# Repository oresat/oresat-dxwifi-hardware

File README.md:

# oresat-dxwifi-hardware
This repository is for the DxWiFi hardware that will fly on the OreSat satellite. DxWiFi is our communication subsystem for high speed data (1 Mbps) using 2.4 GHz WiFi between the spacecraft and ground.

This is hardware for the **satellite** only; please see the other repos if you're looking for the [OreSat Live Handheld Ground Station](https://github.com/oresat/oresat-live-handheld-ground-station) or the [Mini-OreSat testing platform for high altitude balloons](https://github.com/oresat/oresat-live-mini-oresat).

We intend to use "ordinary WiFi" (IEEE 802.11b) as a high speed satellite communication system. What is _not_ ordinary is that we run the radio under the amateur radio rules and regulations (FCC Part 97) and thus can increase power levels and antenna gains necessary to make the link budget work.

### Ordinary WiFi
The plan is to use the Qualcomm Atheros AR9271 USB to WiFi adapter because of the driver support in Linux.

### Non ordinary bi-directional power amplifier
This project is intended to operate under the Amateur Radio Service [47CFR97](https://www.gpo.gov/fdsys/pkg/CFR-1996-title47-vol5/pdf/CFR-1996-title47-vol5-part97.pdf) whereby larger power levels and higher gain directional antennas can be used within the [13 cm band](https://en.wikipedia.org/wiki/13-centimeter_band) to close the link.

NB:  There are other DxWiFi materials on the PSAS GitHub repo, but those repos are deprecated.

Link budgets can be found [here](https://github.com/oresat/oresat-dxwifi-hardware/tree/master/Link-Model).

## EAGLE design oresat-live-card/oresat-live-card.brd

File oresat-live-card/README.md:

---
title: "**OreSat Live / DxWiFi Card**"
subtitle: |
  **Fabrication and Assembly Information**\
  For build TIME-STAMP
fontsize: 10pt
geometry:
  - margin=0.5in
toc: true
toc-depth: 2
colorlinks: true
urlcolor: blue
---

\newpage

# About this Board

## Board Description

TODO: DESCRIBE CARD

## Documentation Links

- OL hardware Git repository: <https://github.com/oresat/oresat-dxwifi-hardware>
- OL software Git reposity: <https://github.com/oresat/oresat-dxwifi-software>
- **TODO:** OL Design Notes + Design Review Notes

## Documentation Files

| Filename                        | Notes                                    |
| ------------------------------- | ---------------------------------------- |
| README.pdf                      | This README file                         |
| PROJECT-NAME-outline.dxf        | Board outline (with holes) in DXF format |
| PROJECT-NAME-pcba.step          | 3D model of PCBA (with components)       |
| PROJECT-NAME-render-bot.jpg     | Render of the top of the 3D model        |
| PROJECT-NAME-render-bot.jpg     | Render of the bottom of the 3D model     |
| PROJECT-NAME-schematic.pdf      | PDF of board schematics                  |

## Contact Information

- Website: <https://www.oresat.org/>
- Email: <oresat@pdx.edu>
- Instagram: @pdxaerospace

## Board Renders

{width=50%}
{width=50%}

\newpage

# Printed Circuit Board (PCB) Fabrication Information

## Board Info

- 4 layer board
- Bounding box is 99.8 x 94.6 mm (3.93 x 3.72 in)
- Board thickness is 1.59 mm (0.063 inch)
- **Important:** See Materials and Stack Up sections below

## Board Requirements

- Design Rules
    - Minimum Trace / Space design rules
       - Outer layers: 0.127 mm (5.0 mil) / 0.127 mm (5.0 mil)
       - Inner layers: 0.127 mm (5.0 mil) / 0.127 mm (5.0 mil)
    - Outer dimension router tolerance: +/- 0.254 mm (10.0 mil)
    - Hole placement tolerance: +/- 0.075 mm (3.0 mil)
    - Inner tab routed slot tolerance: +/- 0.254 mm (10.0 mil)
- Drills
   - Drill Positional Tolerance: 0.051 mm (2.0 mil)
   - Drill Size tolerance: +/- 0.064 mm (2.5 mil)
- Plated/Un-plated holes
  - There are 6 un-plated (NPT) holes
  - There are 1477 plated through (PTH) holes
  - PTH minimum diameter: 0.254 mm (10 mil)
  - PTH minimum annulus: 0.102 mm (4 mil) radius
- Outline/Routing
  - Requires a 1.0 mm or smaller diameter routing bit
- Slots
  - There are no slots.
- Cutouts
  - There are no cutouts
- There are 3 fiducials on the top layer and 3 on the bottom layer.
- Panel tabs ("mouse bites")
   - Card edges must be smooth; no mouse bites or other intrusions into the card outline.
   - If external mouse bites are required, minimize and customer will remove by hand before assembly.
- If not otherwise specified, build to IPC 6012 Class 2 or better.

## Materials

- Controlled impedance
   - The stackup is critical for the performance of high speed signals on this board.
   - As long as the stackup is controlled, the board is not considered controlled impedance.
- Isola FR408HR or material with equivalent Dk.
- Board Surface treatment should be ENIG, althogh immersion Silver is acceptable.
- White silkscreen on top and bottom surface
- Taiyo PSR-4000 or equivalent soldermask on top and bottom, no requirements for color.

## Stack Up

| Layer         | Thickness           | Notes                                        |
|---------------|---------------------|----------------------------------------------|
| Top Copper    | 0.043 mm /  1.7 mil |  Layer 1 foil, 1 oz Cu after plating         |
| prepreg       | 0.200 mm /  7.9 mil |  Prepreg - Isola FR408HR 2113                |
| Layer 2       | 0.018 mm /  0.7 mil |  Layer 2 foil, 0.5 oz Cu                     |
| Core          | 0.991 mm /   39 mil |  Core Isola FR408HR                          |
| Layer 3       | 0.018 mm /  0.7 mil |  Layer 3 foil, 0.5 oz Cu                     |
| prepreg       | 0.200 mm /  7.9 mil |  Prepreg - Isola FR408HR 2113                |
| Bottom Copper | 0.043 mm /  1.7 mil |  Layer 4 foil, 1 oz copper after plating     |
| **Total Stackup** | **1.588 mm / 62.5 mil** |                                      |

## Array / Panel Information

- Coordinate with Contract Manufacturer (CM) for optimal size of this panel.
- If no feedback from CM, then produce single boards (no panel).

## Fabrication Files

### IPC-2581 File

| Filename                 | Notes                                   |
| ------------------------ | --------------------------------------- |
| PROJECT-NAME-ipc2581.xml | IPC-2581 board information file         |

### Legacy PCB Files

| Filename                      | Notes                                         |
| ------------------------------| --------------------------------------------- |
| PROJECT-NAME-Edge_Cuts.gbr    | RS274X file for the dimension (outline) layer |
| PROJECT-NAME-F_Silkscreen.gbr | RS274X file for the top silkscreen            |
| PROJECT-NAME-F_Mask.gbr       | RS274X file for the top soldermask            |
| PROJECT-NAME-F_Cu.gbr         | RS274X file for the top copper layer          |
| PROJECT-NAME-In1_Cu.gbr       | RS274X file for the layer 2 copper            |
| PROJECT-NAME-In2_Cu.gbr       | RS274X file for the layer 3 copper            |
| PROJECT-NAME-B_Cu.gbr         | RS274X file for the bottom copper layer       |
| PROJECT-NAME-B_Mask.gbr       | RS274X file for the bottom soldermask         |
| PROJECT-NAME-B_Silkscreen.gbr | RS274X file for the bottom silkscreen         |
| PROJECT-NAME-NPTH.drl         | Excellon file for non-plated through holes    |
| PROJECT-NAME-PTH.drl          | Excellon file for plated through holes        | 

\newpage

# Printed Circuit Board Assembly (PCBA) Information

## Assembly Info

- There are components are on the top and bottom side of the board.
- This PCBA is mostly surface mount (SMT) with a few (THT) components.

## Assembly Requirements

- Assemble to IPC Class 2 or better
- Bake components that are not moisture sealed to appropriate levels as required.
- Solder paste MUST be leaded.
- Aqueous flux and wash strongly preferred.
   - Clean to NASA Standard "Visibly Clean (VC)": No particles or residues are visible to the naked eye.
- No conformal coating.
- Ship in antistatic protective bag

## Component Specific Assembly Information

- SMPM connectors (J3, J4) should be hand-added according to the Oresat SOP.

## Assembly Files

### IPC-2581 File

| Filename                 | Notes                           |
| ------------------------ | ------------------------------- |
| PROJECT-NAME-ipc2581.xml | IPC-2581 board information file |

### Bill of Materials (BOM)

| Filename             | Description                            |
| -------------------- | -------------------------------------- |
| PROJECT-NAME-bom.csv | BOM in Comma Separated Variable format |

### Solder Paste Stencils

| Filename                 | Notes                                            |
| ------------------------ | ------------------------------------------------ |
| PROJECT-NAME-B_Paste.gbr | RS274X file for top/front solder paste stencil   |
| PROJECT-NAME-F_Paste.gbr | RS274X file for bottom/back solder paste stencil |

### Mounting/Placement Location

| Filename            | Description                                 |
| ------------------- | ------------------------------------------- |
| PROJECT-NAME-3u.pos | Pick and place locations for components     |

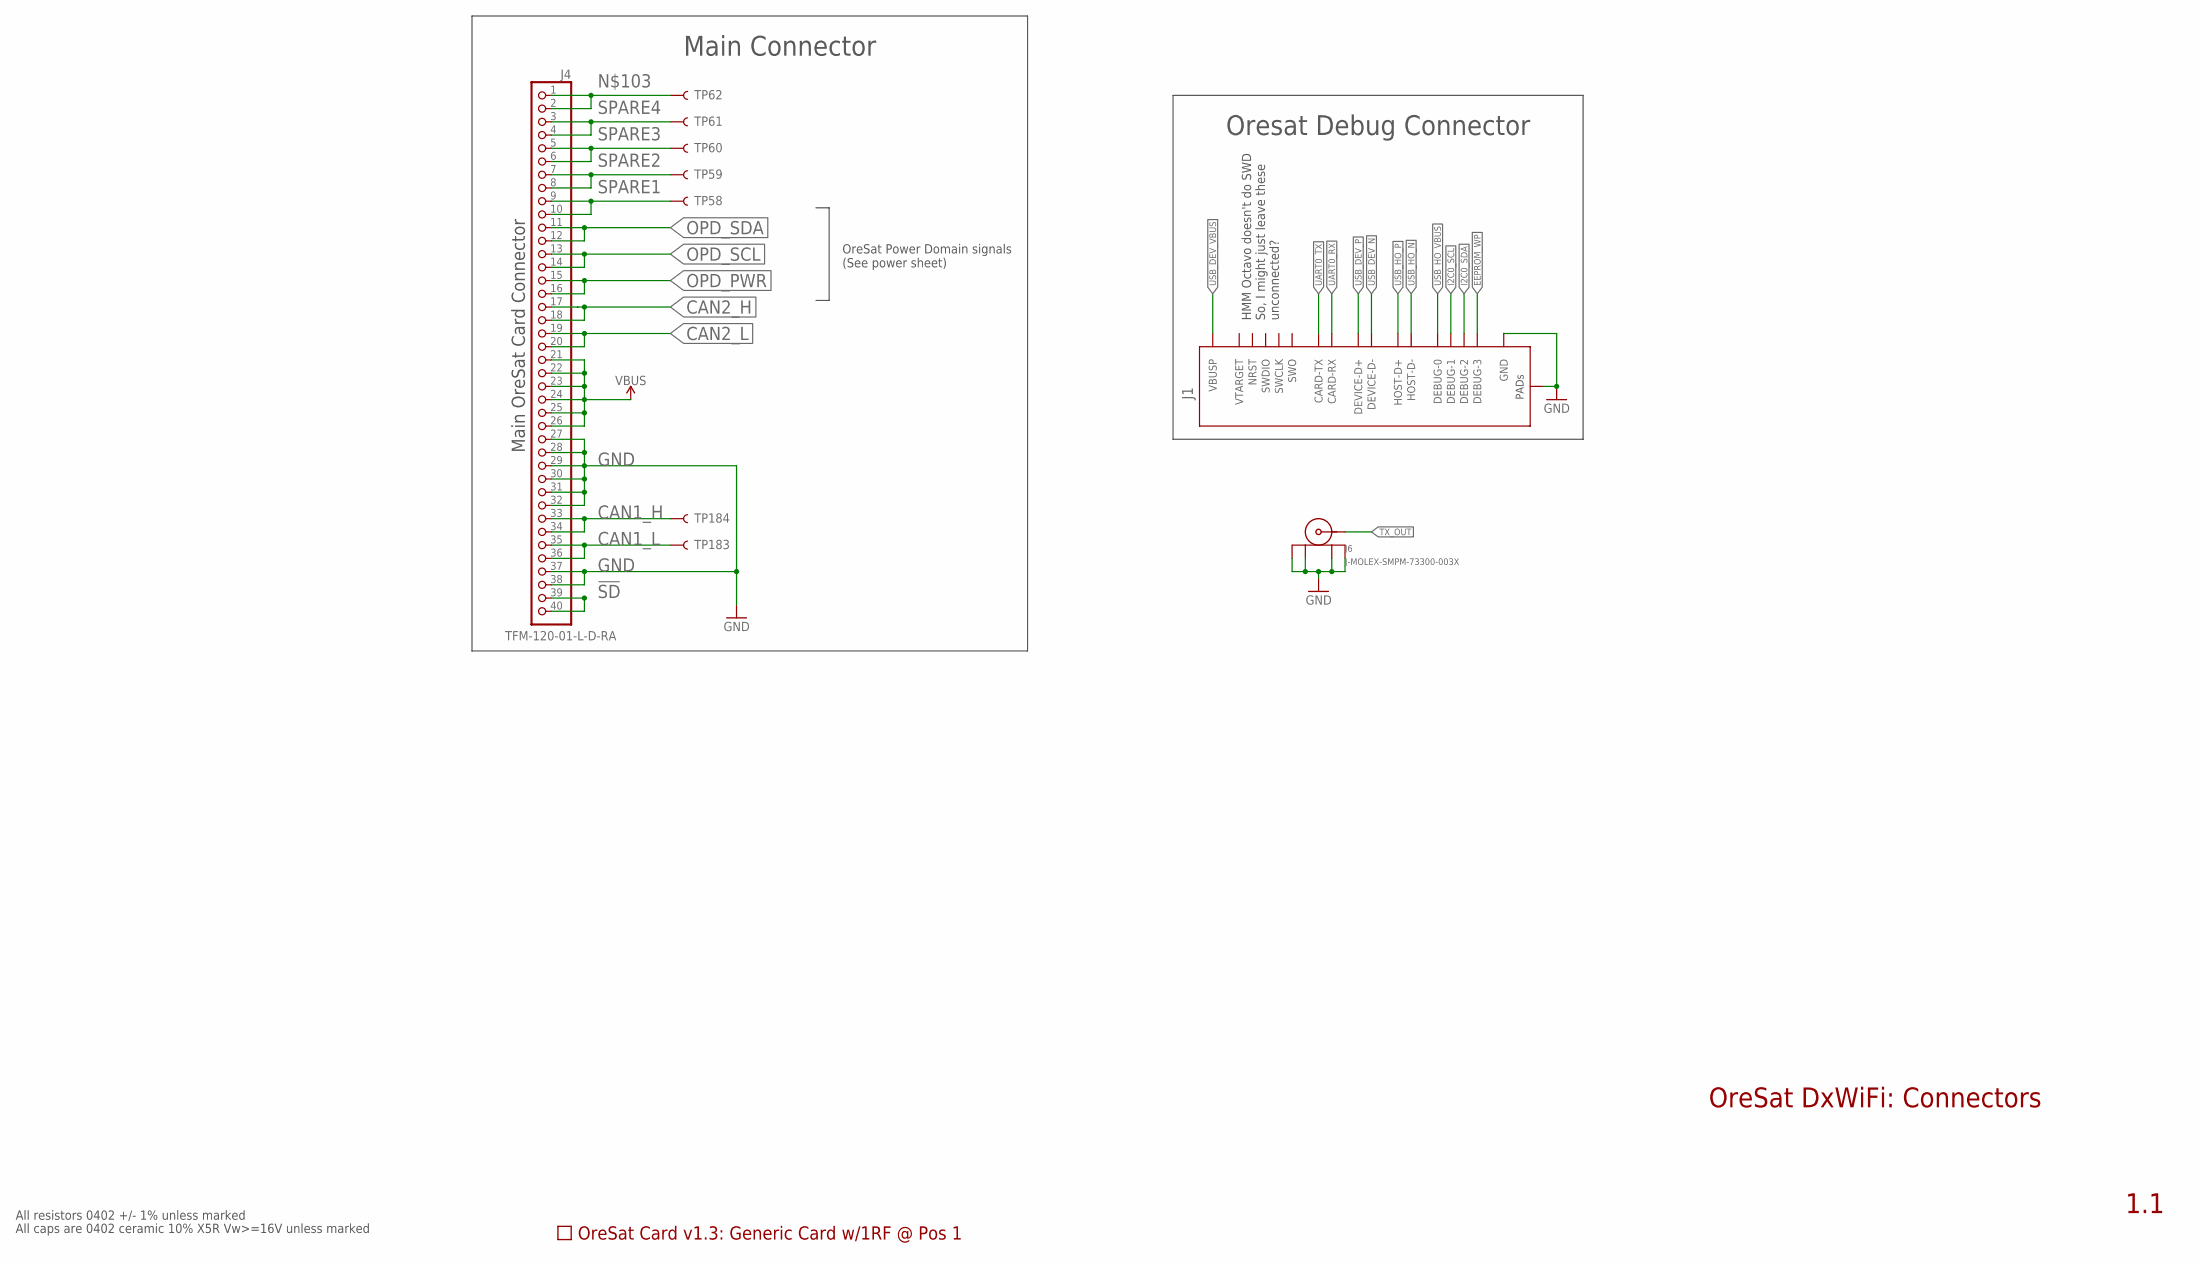
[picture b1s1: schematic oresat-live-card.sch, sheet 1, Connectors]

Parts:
J1: ORESAT-DEBUG-CONNECTOR-CARD; TE_2-1734592-0
J4: TFM-120-01-L-D-RA; J-SAMTEC-TFM-120-X1-XXX-D-RA
J6: J-MOLEX-SMPM-73300-003X; J-MOLEX-SMPM-073300-003X
PCB1: ORESAT-CARD-V1.3-GENERIC-1RF-POS1
TP58, TP59, TP60, TP61, TP62, TP183, TP184: TEST-POINT3X4; PAD.03X.04

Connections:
!SD: J4.39, J4.40
CAN1_H: J4.33, J4.34, TP184.1
CAN1_L: J4.35, J4.36, TP183.1
CAN2_H: J4.17, J4.18; also elsewhere on the board
CAN2_L: J4.19, J4.20; also elsewhere on the board
EEPROM_WP: J1.20 (DEBUG-3); also elsewhere on the board
GND: J1.3 (GND), J1.6 (GND), J1.9 (GND), J1.PAD1 (PAD), J1.PAD2 (PAD), J4.27, J4.28, J4.29, J4.30, J4.31, J4.32, J4.37, J4.38, J6.P$1 (SHIELD3), J6.P$2 (SHIELD2), J6.P$3 (SHIELD1), J6.P$4 (SHIELD); also elsewhere on the board
I2C0_SCL: J1.18 (DEBUG-1); also elsewhere on the board
I2C0_SDA: J1.19 (DEBUG-2); also elsewhere on the board
unnamed: J4.1, J4.2, TP62.1
OPD_PWR: J4.15, J4.16; also elsewhere on the board
OPD_SCL: J4.13, J4.14; also elsewhere on the board
OPD_SDA: J4.11, J4.12; also elsewhere on the board
SPARE1: J4.9, J4.10, TP58.1
SPARE2: J4.7, J4.8, TP59.1
SPARE3: J4.5, J4.6, TP60.1
SPARE4: J4.3, J4.4, TP61.1
TX_OUT: J6.RF (CENTER); also elsewhere on the board
UART0_RX: J1.12 (CARD-RX); also elsewhere on the board
UART0_TX: J1.13 (CARD-TX); also elsewhere on the board
USB_DEV_N: J1.5 (DEVICE-D-); also elsewhere on the board
USB_DEV_P: J1.4 (DEVICE-D+); also elsewhere on the board
USB_DEV_VBUS: J1.1 (VBUSP), J1.2 (VBUSP); also elsewhere on the board
USB_HO_N: J1.8 (HOST-D-); also elsewhere on the board
USB_HO_P: J1.7 (HOST-D+); also elsewhere on the board
USB_HO_VBUS: J1.17 (DEBUG-0); also elsewhere on the board
VBUS: J4.21, J4.22, J4.23, J4.24, J4.25, J4.26; also elsewhere on the board

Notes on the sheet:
OreSat DxWiFi: Connectors
1.1
All resistors 0402 +/- 1% unless marked
All caps are 0402 ceramic 10% X5R Vw>=16V unless marked
Main Connector
Main OreSat Card Connector
OreSat Power Domain signals (See power sheet)
HMM Octavo doesn't do SWD So, I might just leave these unconnected?
Oresat Debug Connector

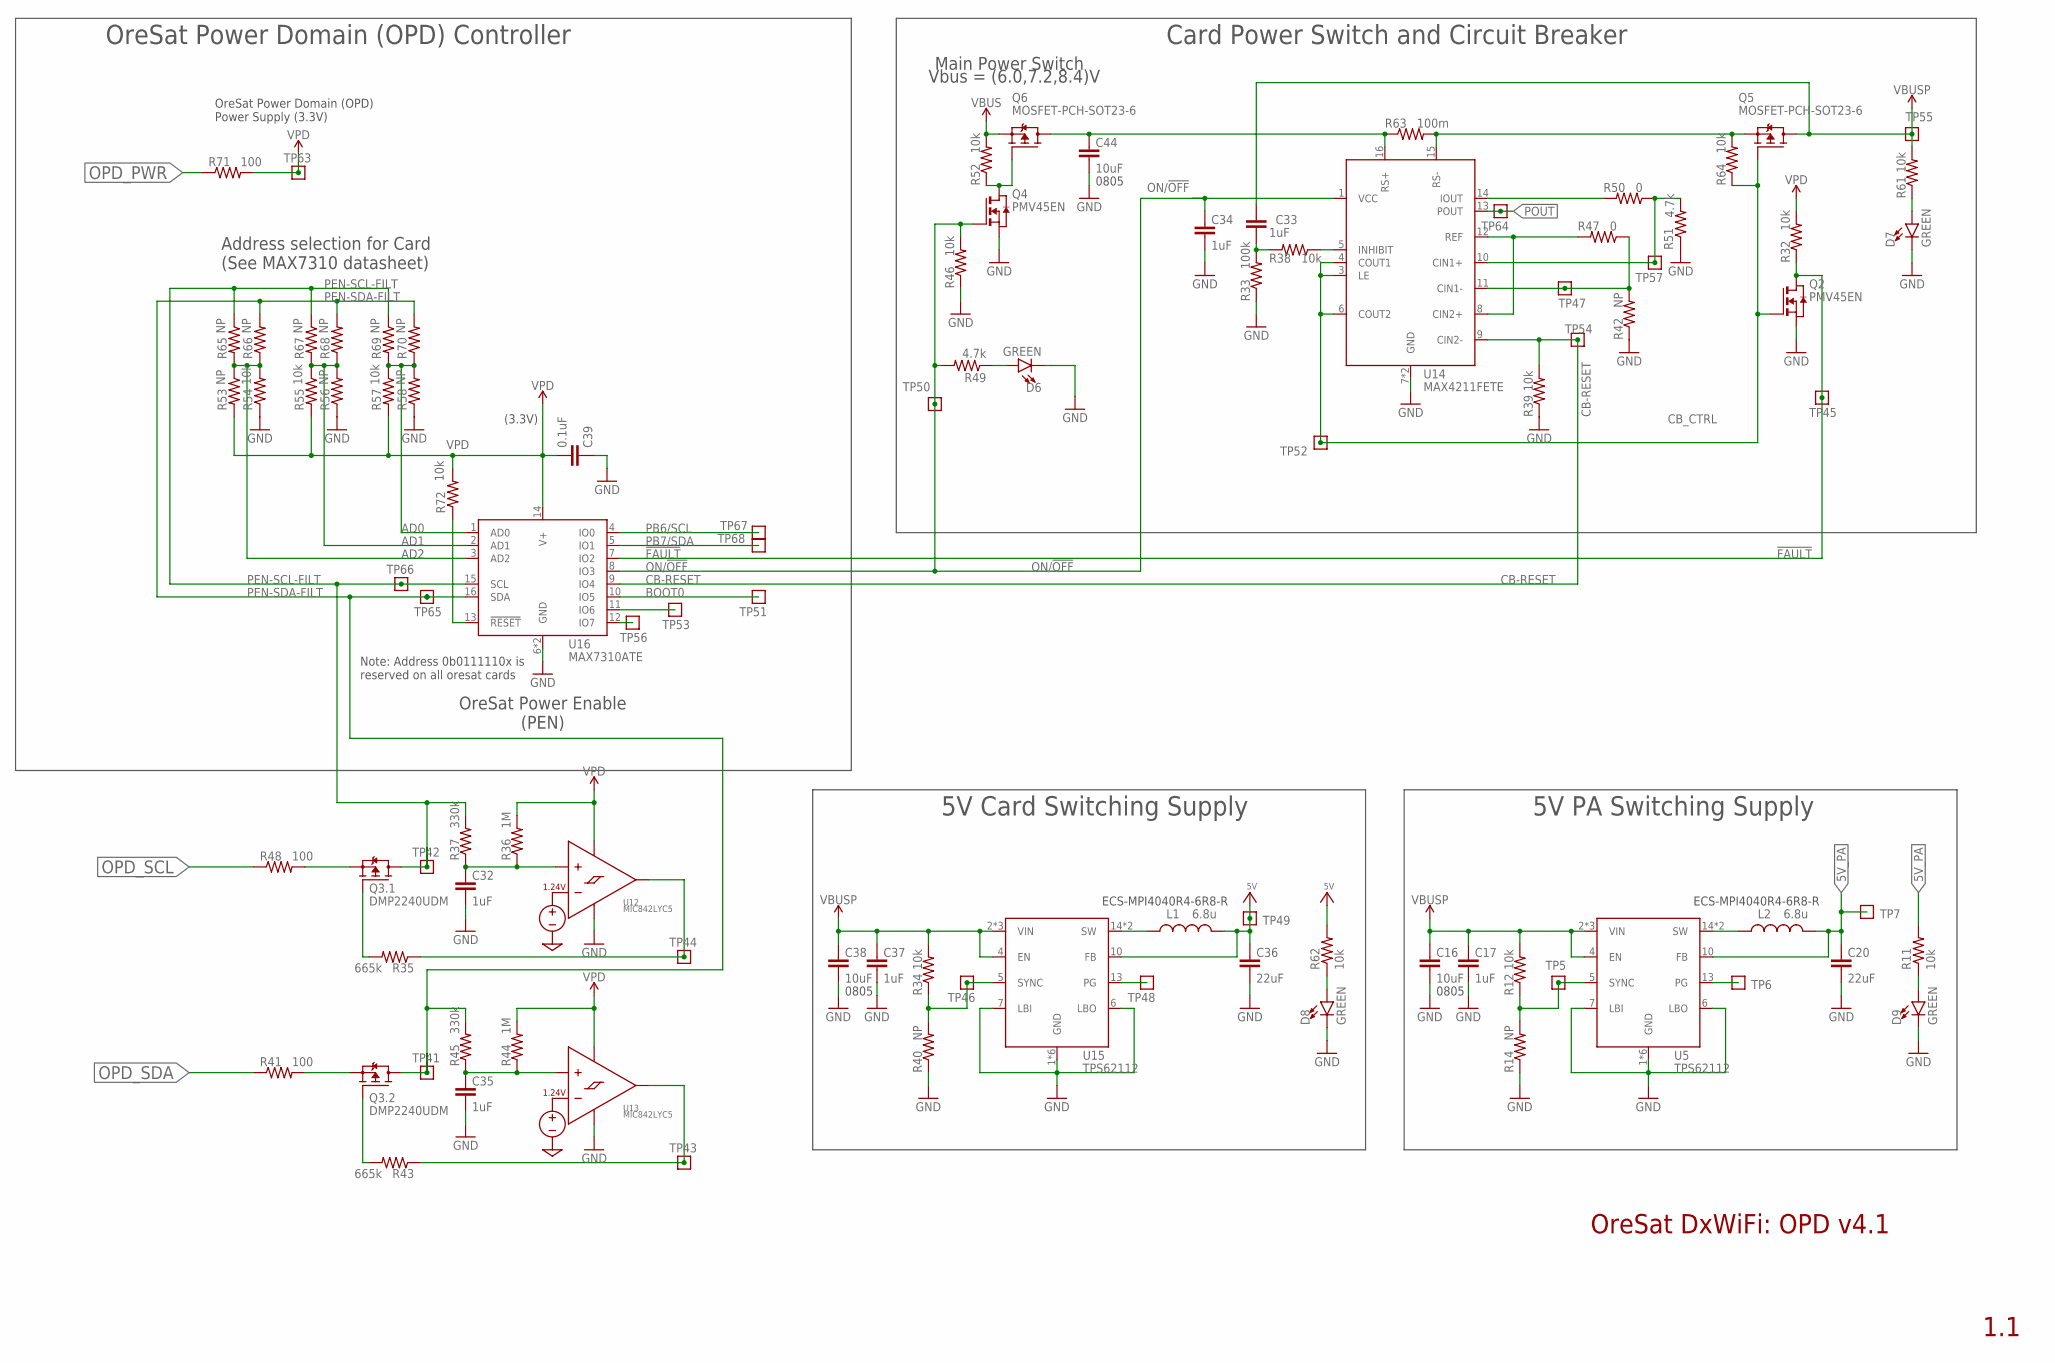
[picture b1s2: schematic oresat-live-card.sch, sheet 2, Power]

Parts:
C16, C38, C44: 10uF; .0805-B
C17, C34, C37: 1uF; .0603-A
C20: 22uF; C1210; MPN GCJ32ER71C226KE01L
C32, C35: 1uF; .0805-B-NOSILK
C33: 1uF; .0603-A; MPN CL05B104KO5NNNC
C36: 22uF; C1210
C39: 0.1uF; .0603-A
D6, D7, D9: GREEN; LED-0603; MANUFACTURER_PART_NUMBER 150060VS55040; DIGI-KEY_PART_NUMBER 732-12017-1-ND
D8: GREEN; LED-0603; MANUFACTURE_PART_NUMBER 150060VS55040; DIGI-KEY_PART_NUMBER 732-12017-1-ND
L1, L2: 6.8u; ECS-MPI4040
Q2, Q4: PMV45EN; SOT23; MPN PMV45EN2R
Q3: DMP2240UDM; SOT23-6
Q5, Q6: MOSFET-PCH-SOT23-6; SOT23-6; MPN DMP3050LVT-7
R11, R12, R32, R34, R39, R46, R52, R61, R62, R64, R72: 10k; .0603-A
R14, R40, R42, R53, R56, R58, R65, R66, R67, R68, R69, R70: NP; .0603-A; MPN RC1005F6653CS
R33: 100k; .0603-A; MPN RC1005F6653CS
R35, R43: 665k; .0603-A
R36, R44: 1M; .0603-A
R37, R45: 330k; .0603-A
R38, R54, R55, R57: 10k; .0603-A; MPN RC1005F6653CS
R41, R48, R71: 100; .0603-A
R47, R50: 0; .0603-A
R49: 4.7k; .0603-A
R51: 4.7k; .0603-A; MPN RC1005F6653CS
R63: 100m; R1206
TP5, TP6, TP7, TP41, TP42, TP43, TP44, TP45, TP46, TP47, TP48, TP49, TP50, TP51, TP52, TP53, TP54, TP55, TP56, TP57, TP63, TP64, TP65, TP66, TP67, TP68: TEST-POINT; 2MM-TEST-POINT
U5, U15: TPS62112; S-PVQFN-16
U12, U13: MIC842LYC5; SC70-5
U14: MAX4211FETE; QFN65P400X400X80-17T210
U16: MAX7310ATE; QFN65P400X400X80-17T210; MPN MAX7310ATE

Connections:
5V: C36.1, L1.2, R62.2, TP49.1, U15.10 (FB); also elsewhere on the board
5V_PA: C20.1, L2.2, R11.2, TP7.1, U5.10 (FB); also elsewhere on the board
!FAULT: Q2.3 (D), R32.1, TP45.1, U16.7 (IO2)
AD0: R57.1, R58.2, R69.2, R70.1, U16.1 (AD0)
AD1: R55.1, R56.2, R67.2, R68.1, U16.2 (AD1)
AD2: R53.1, R54.2, R65.2, R66.1, U16.3 (AD2)
BOOT0: TP51.1, U16.10 (IO5)
CB-RESET: R39.2, TP54.1, U14.9 (CIN2-), U16.9 (IO4)
CB_CTRL: Q2.1 (G), Q5.3 (G), R64.1, TP52.1, U14.3 (LE), U14.4 (COUT1), U14.6 (COUT2)
GND: C16.2, C17.2, C20.2, C32.2, C34.2, C35.2, C36.2, C37.2, C38.2, C39.1, C44.2, D6.C, D7.C, D8.C, D9.C, Q2.2 (S), Q4.2 (S), R14.1, R33.1, R39.1, R40.1, R42.1, R46.1, R51.1, R54.1, R56.1, R58.1, U5.1 (GND), U5.6 (LBO), U5.7 (LBI), U5.9 (GND), U5.11 (GND), U5.12 (GND), U5.16 (GND), U5.PAD (GND), U12.2 (GND), U13.2 (GND), U14.7 (GND), U14.EPAD (GND), U15.1 (GND), U15.6 (LBO), U15.7 (LBI), U15.9 (GND), U15.11 (GND), U15.12 (GND), U15.16 (GND), U15.PAD (GND), U16.6 (GND), U16.EPAD (GND); also elsewhere on the board
IOUT: R50.2, U14.14 (IOUT)
unnamed: C32.1, R36.1, R37.1, U12.1 (INP)
unnamed: R35.1, TP44.1, U12.4 (OUT)
unnamed: TP56.1, U16.12 (IO7)
unnamed: TP6.1, U5.13 (PG)
unnamed: C44.1, Q6.1 (D), Q6.2 (D), Q6.5 (D), Q6.6 (D), R63.1, U14.16 (RS+)
unnamed: Q5.4 (S), R63.2, R64.2, U14.15 (RS-)
unnamed: C35.1, R44.1, R45.1, U13.1 (INP)
unnamed: D9.A, R11.1
unnamed: Q3.3 (G), R43.2
unnamed: Q3.1 (G), R35.2
unnamed: D7.A, R61.1
unnamed: D8.A, R62.1
unnamed: TP53.1, U16.11 (IO6)
unnamed: Q3.5 (S), R48.2
unnamed: D6.A, R49.1
unnamed: Q3.2 (S), R41.2
unnamed: R43.1, TP43.1, U13.4 (OUT)
unnamed: R72.1, U16.13 (!RESET)
unnamed: Q4.3 (D), Q6.3 (G), R52.1
unnamed: R50.1, R51.2, TP57.1, U14.10 (CIN1+)
unnamed: R42.2, R47.1, TP47.1, U14.11 (CIN1-)
unnamed: R47.2, U14.8 (CIN2+), U14.12 (REF)
unnamed: C33.1, R33.2, R38.2
unnamed: R38.1, U14.5 (INHIBIT)
ON/!OFF: C34.1, Q4.1 (G), R46.2, R49.2, TP50.1, U14.1 (VCC), U16.8 (IO3)
OPD_PWR: R71.1; also elsewhere on the board
OPD_SCL: R48.1; also elsewhere on the board
OPD_SDA: R41.1; also elsewhere on the board
PB6/SCL: TP67.1, U16.4 (IO0)
PB7/SDA: TP68.1, U16.5 (IO1)
PEN-SCL-FILT: Q3.6 (D), R37.2, R65.1, R67.1, R69.1, TP42.1, TP66.1, U16.15 (SCL)
PEN-SDA-FILT: Q3.4 (D), R45.2, R66.2, R68.2, R70.2, TP41.1, TP65.1, U16.16 (SDA)
POUT: TP64.1, U14.13 (POUT)
TPS62111-PG: TP48.1, U15.13 (PG)
TPS62111-SYNC: R34.1, R40.2, TP46.1, U15.5 (SYNC)
TPS62111-SYNC1: R12.1, R14.2, TP5.1, U5.5 (SYNC)
TPS62111_SW: L1.1, U15.14 (SW), U15.15 (SW)
TPS62111_SW1: L2.1, U5.14 (SW), U5.15 (SW)
VBUS: Q6.4 (S), R52.2; also elsewhere on the board
VBUSP: C16.1, C17.1, C33.2, C37.1, C38.1, Q5.1 (D), Q5.2 (D), Q5.5 (D), Q5.6 (D), R12.2, R34.2, R61.2, TP55.1, U5.2 (VIN), U5.3 (VIN), U5.4 (EN), U5.8 (VIN), U15.2 (VIN), U15.3 (VIN), U15.4 (EN), U15.8 (VIN)
VPD: C39.2, R32.2, R36.2, R44.2, R53.2, R55.2, R57.2, R71.2, R72.2, TP63.1, U12.5 (VDD), U13.5 (VDD), U16.14 (V+)

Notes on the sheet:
0805
ECS-MPI4040R4-6R8-R
5V Card Switching Supply
1.1
Main Power Switch
OreSat Power Enable (PEN)
Address selection for Card (See MAX7310 datasheet)
(3.3V)
Vbus = (6.0,7.2,8.4)V
OreSat Power Domain (OPD) Power Supply (3.3V)
OreSat Power Domain (OPD) Controller
Card Power Switch and Circuit Breaker
Note: Address 0b0111110x is reserved on all oresat cards
OreSat DxWiFi: OPD v4.1
5V PA Switching Supply

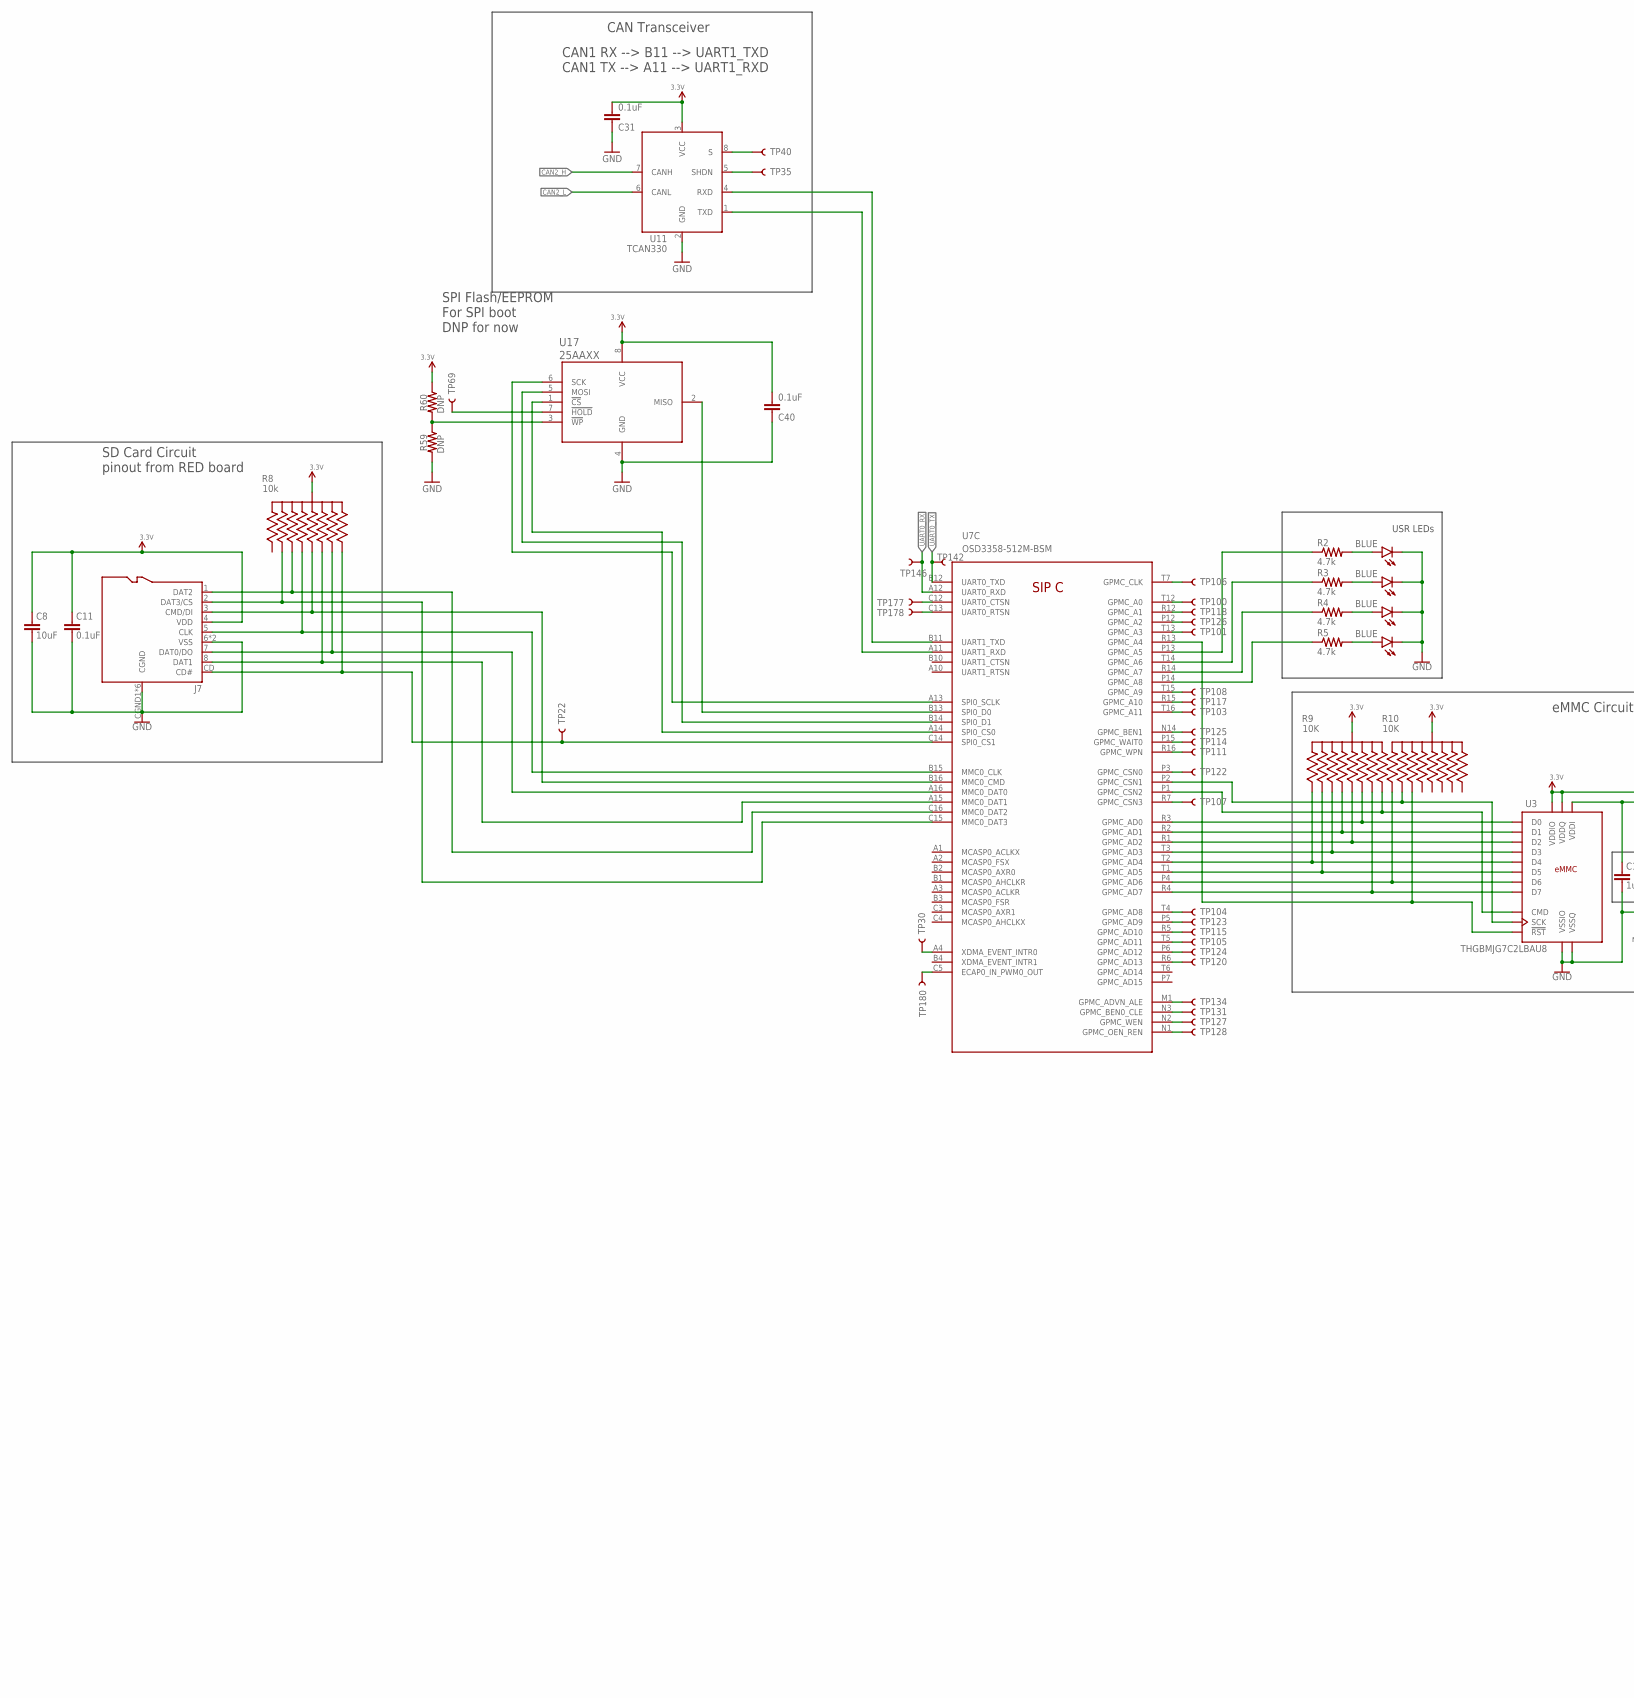
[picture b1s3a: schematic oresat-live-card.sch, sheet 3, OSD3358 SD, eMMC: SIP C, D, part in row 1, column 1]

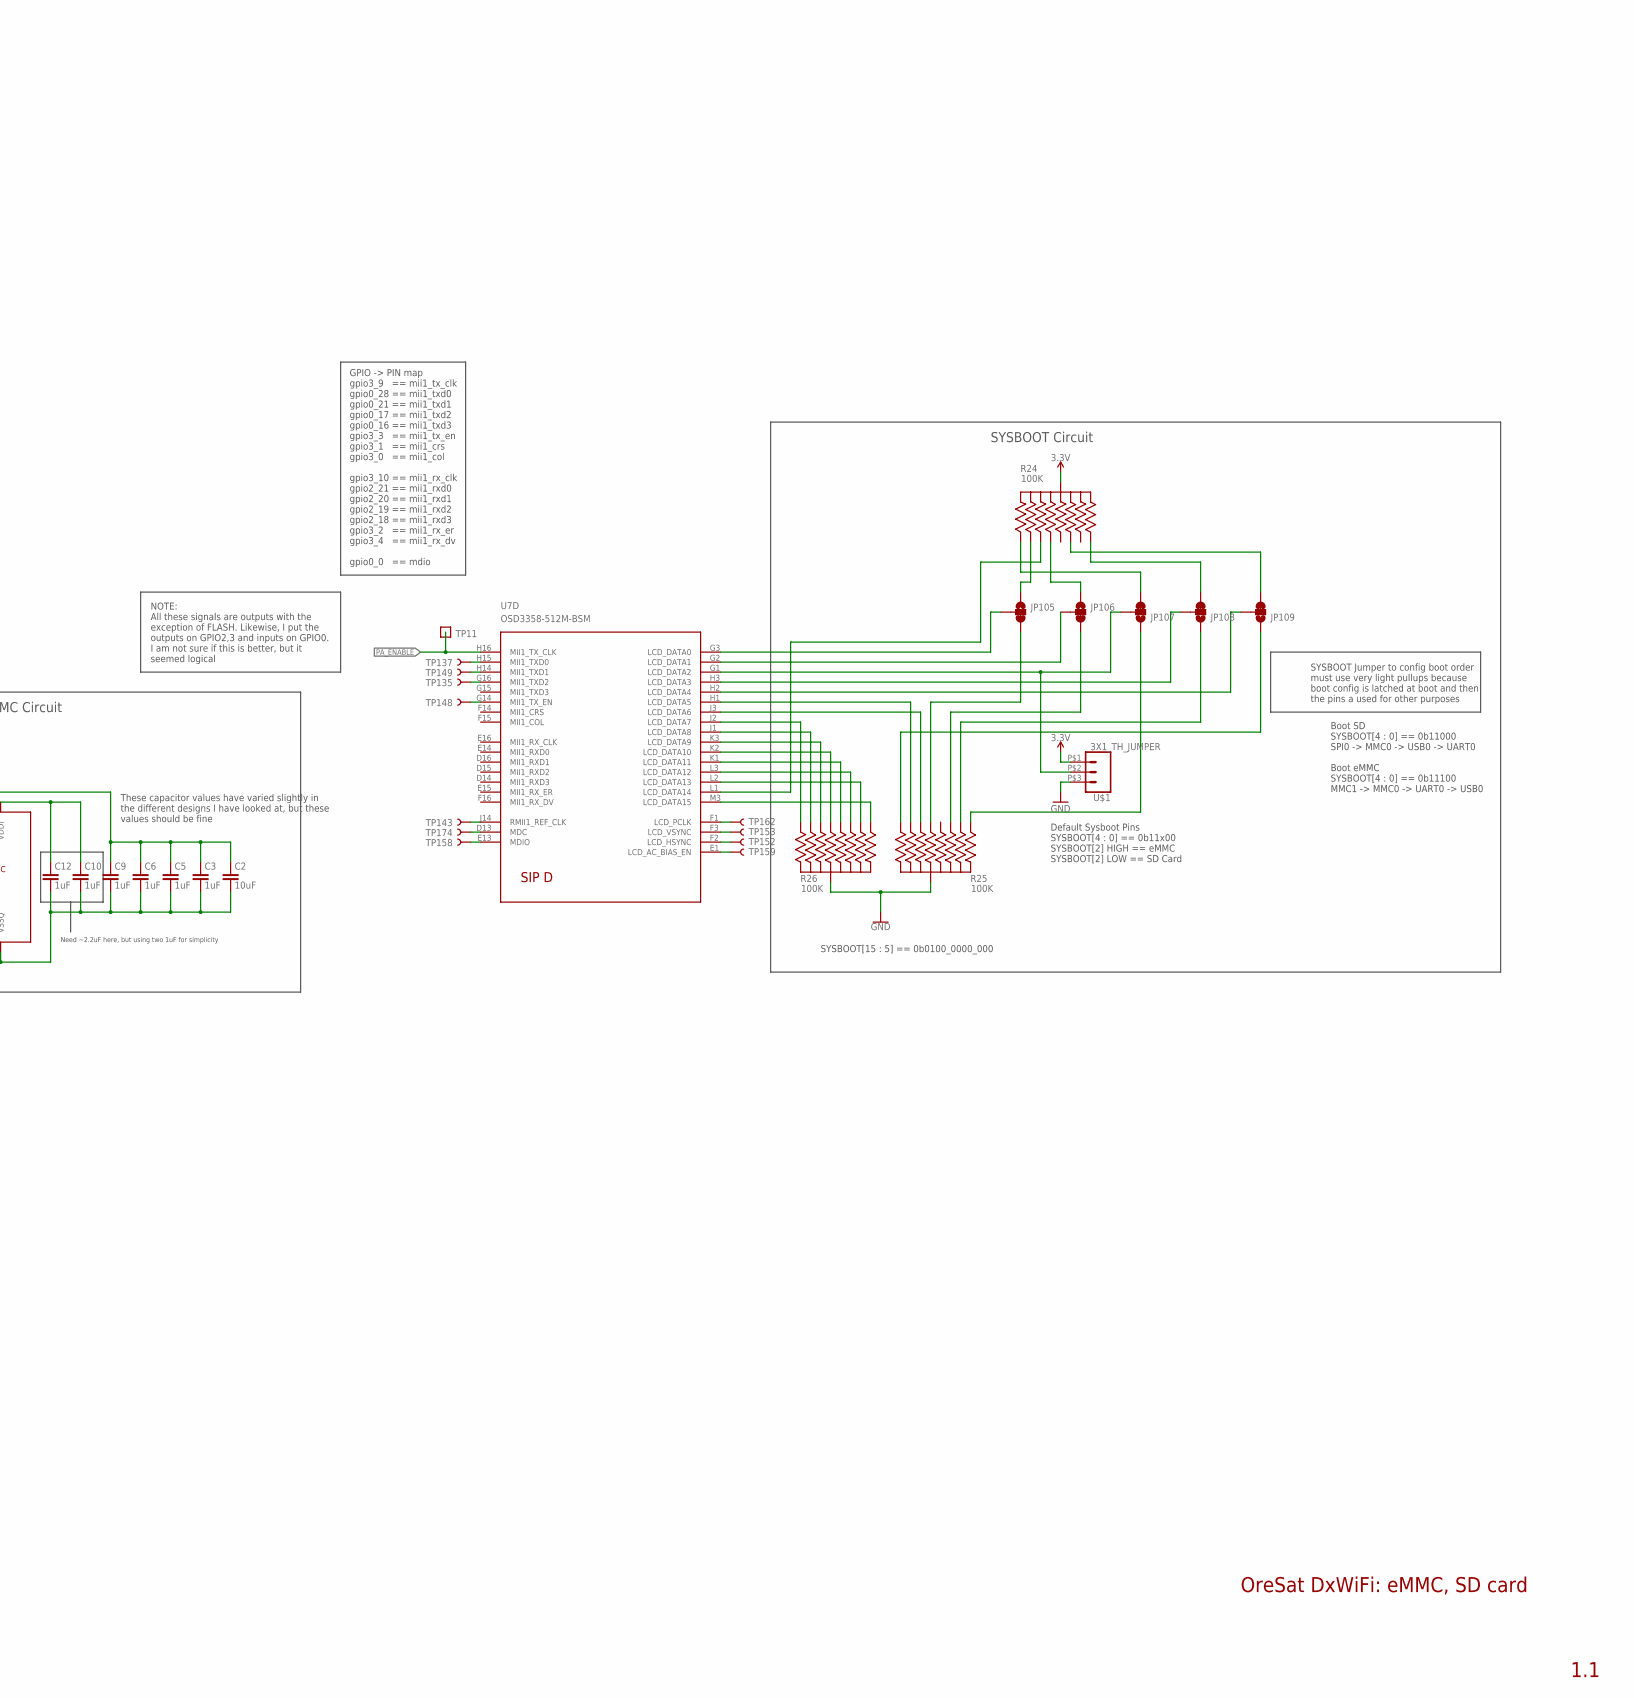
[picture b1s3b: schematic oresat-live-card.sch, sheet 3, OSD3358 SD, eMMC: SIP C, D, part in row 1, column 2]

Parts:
C2, C8: 10uF; .0805-B
C3, C5, C6, C9, C10, C12: 1uF; .0603-A
C11, C31, C40: 0.1uF; .0603-A
D2, D3, D4, D5: BLUE; LED-0603
J7: DM3BT-DSF-PEJS
JP105, JP106, JP107, JP108, JP109: JUMPER-SMT_3_1-NC_TRACE_SILK; SMT-JUMPER_3_1-NC_TRACE_SILK
R2, R3, R4, R5: 4.7k; .0603-A
R8: 10k; ARRAY_EXBA-M; MPN EXB-A10P103J
R9, R10: 10K; ARRAY_EXBA-M; MPN EXB-A10P103J
R24, R25, R26: 100K; ARRAY_EXBA-M; MPN EXB-A10P104J
R59, R60: DNP; .0603-A
TP11: TEST-POINT; 2MM-TEST-POINT
TP22, TP30, TP35, TP40, TP69, TP100, TP101, TP103, TP104, TP105, TP106, TP107, TP108, TP111, TP114, TP115, TP117, TP118, TP120, TP122, TP123, TP124, TP125, TP126, TP127, TP128, TP131, TP134, TP135, TP137, TP142, TP143, TP146, TP148, TP149, TP152, TP153, TP158, TP159, TP162, TP174, TP177, TP178, TP180: TEST-POINT3X4; PAD.03X.04
U3: THGBMJG7C2LBAU8; BGA-153(11.5X13)(EMMC-BA); MPN THGBMJG7C2LBAU8
U7: OSD3358-512M-BSM; OSD335X-BGA-256
U11: TCAN330; SOT23-8_TI-DCN
U17: 25AAXX; SOIC8
U$1: 3X1_TH_JUMPER; 3X1

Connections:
3.3V: C2.1, C3.1, C5.1, C6.1, C8.1, C9.1, C11.1, C31.2, C40.2, J7.4 (VDD), R8.5 (55), R8.10 (55), R9.5 (55), R9.10 (55), R10.5 (55), R10.10 (55), R24.5 (55), R24.10 (55), R60.1, U3.C6 (VDDQ), U3.E6 (VDDIO), U3.F5 (VDDIO), U3.J10 (VDDIO), U3.K9 (VDDIO), U3.M4 (VDDQ), U3.N4 (VDDQ), U3.P3 (VDDQ), U3.P5 (VDDQ), U11.3 (VCC), U17.8 (VCC), U$1.P$1 (1); also elsewhere on the board
CAN2_H: U11.7 (CANH); also elsewhere on the board
CAN2_L: U11.6 (CANL); also elsewhere on the board
GND: C2.2, C3.2, C5.2, C6.2, C8.2, C9.2, C10.2, C11.2, C12.2, C31.1, C40.1, D2.C, D3.C, D4.C, D5.C, J7.6 (VSS), J7.CGND1 (CGND), J7.CGND2 (CGND), J7.CGND3 (CGND), J7.CGND4 (CGND), J7.CGND5 (CGND), J7.CGND6 (CGND), J7.GND (VSS), R25.5 (55), R25.10 (55), R26.5 (55), R26.10 (55), R59.2, U3.A6 (VSSIO), U3.C4 (VSSQ), U3.E7 (VSSIO), U3.G5 (VSSIO), U3.H10 (VSSIO), U3.J5 (VSSIO), U3.K8 (VSSIO), U3.N2 (VSSQ), U3.N5 (VSSQ), U3.P4 (VSSQ), U3.P6 (VSSQ), U11.2 (GND), U17.4 (GND), U$1.P$3 (3); also elsewhere on the board
unnamed: D5.A, R5.2
unnamed: J7.1 (DAT2), R8.2 (22), U7.C16 (MMC0_DAT2)
unnamed: J7.2 (DAT3/CS), R8.9 (99), U7.C15 (MMC0_DAT3)
unnamed: J7.3 (CMD/DI), R8.3 (33), U7.B16 (MMC0_CMD)
unnamed: J7.5 (CLK), R8.8 (88), U7.B15 (MMC0_CLK)
unnamed: J7.7 (DAT0/DO), R8.4 (44), U7.A16 (MMC0_DAT0)
unnamed: J7.8 (DAT1), R8.7 (77), U7.A15 (MMC0_DAT1)
unnamed: J7.CD (CD#), R8.6 (66), TP22.1, U7.C14 (SPI0_CS1)
unnamed: U7.B11 (UART1_TXD), U11.4 (RXD)
unnamed: U7.A11 (UART1_RXD), U11.1 (TXD)
unnamed: TP40.1, U11.8 (S)
unnamed: TP35.1, U11.5 (SHDN)
unnamed: JP105.3, R25.3 (33)
unnamed: JP105.1, R24.9 (99)
unnamed: JP106.1, R24.8 (88)
unnamed: JP107.3, R24.1 (11)
unnamed: JP109.3, R24.7 (77)
unnamed: JP108.3, R24.6 (66)
unnamed: U7.A13 (SPI0_SCLK), U17.6 (SCK)
unnamed: U7.B13 (SPI0_D0), U17.2 (MISO)
unnamed: U7.B14 (SPI0_D1), U17.5 (MOSI)
unnamed: U7.A14 (SPI0_CS0), U17.1 (!CS)
unnamed: TP30.1, U7.A4 (XDMA_EVENT_INTR0)
unnamed: TP180.1, U7.C5 (ECAP0_IN_PWM0_OUT)
unnamed: TP104.1, U7.T4 (GPMC_AD8)
unnamed: TP123.1, U7.P5 (GPMC_AD9)
unnamed: TP115.1, U7.R5 (GPMC_AD10)
unnamed: TP105.1, U7.T5 (GPMC_AD11)
unnamed: TP124.1, U7.P6 (GPMC_AD12)
unnamed: TP120.1, U7.R6 (GPMC_AD13)
unnamed: TP125.1, U7.N14 (GPMC_BEN1)
unnamed: TP114.1, U7.P15 (GPMC_WAIT0)
unnamed: TP111.1, U7.R16 (GPMC_WPN)
unnamed: TP177.1, U7.C12 (UART0_CTSN)
unnamed: TP178.1, U7.C13 (UART0_RTSN)
unnamed: TP162.1, U7.F1 (LCD_PCLK)
unnamed: TP153.1, U7.F3 (LCD_VSYNC)
unnamed: TP152.1, U7.F2 (LCD_HSYNC)
unnamed: TP159.1, U7.E1 (LCD_AC_BIAS_EN)
unnamed: TP143.1, U7.J14 (RMII1_REF_CLK)
unnamed: TP174.1, U7.D13 (MDC)
unnamed: TP158.1, U7.E13 (MDIO)
unnamed: TP137.1, U7.H15 (MII1_TXD0)
unnamed: TP149.1, U7.H14 (MII1_TXD1)
unnamed: TP135.1, U7.G16 (MII1_TXD2)
unnamed: TP106.1, U7.T7 (GPMC_CLK)
unnamed: TP100.1, U7.T12 (GPMC_A0)
unnamed: TP118.1, U7.R12 (GPMC_A1)
unnamed: TP126.1, U7.P12 (GPMC_A2)
unnamed: TP101.1, U7.T13 (GPMC_A3)
unnamed: D4.A, R4.2
unnamed: D3.A, R3.2
unnamed: TP108.1, U7.T15 (GPMC_A9)
unnamed: TP117.1, U7.R15 (GPMC_A10)
unnamed: TP103.1, U7.T16 (GPMC_A11)
unnamed: TP122.1, U7.P3 (GPMC_CSN0)
unnamed: TP107.1, U7.R7 (GPMC_CSN3)
unnamed: D2.A, R2.2
unnamed: TP134.1, U7.M1 (GPMC_ADVN_ALE)
unnamed: TP131.1, U7.N3 (GPMC_BEN0_CLE)
unnamed: TP127.1, U7.N2 (GPMC_WEN)
unnamed: TP128.1, U7.N1 (GPMC_OEN_REN)
unnamed: TP148.1, U7.G14 (MII1_TX_EN)
unnamed: JP106.3, R25.2 (22)
unnamed: JP107.1, R25.1 (11)
unnamed: JP108.1, R25.9 (99)
unnamed: JP109.1, R25.6 (66)
unnamed: R59.1, R60.2, U17.3 (!WP)
unnamed: TP69.1, U17.7 (!HOLD)
unnamed: JP105.2, U7.G3 (LCD_DATA0)
unnamed: JP106.2, U7.G2 (LCD_DATA1)
unnamed: JP107.2, U7.G1 (LCD_DATA2), U$1.P$2 (2)
unnamed: JP108.2, U7.H3 (LCD_DATA3)
unnamed: JP109.2, U7.H2 (LCD_DATA4)
unnamed: R25.4 (44), U7.H1 (LCD_DATA5)
unnamed: R25.7 (77), U7.J3 (LCD_DATA6)
unnamed: R26.4 (44), U7.J1 (LCD_DATA8)
unnamed: R26.7 (77), U7.K3 (LCD_DATA9)
unnamed: R26.3 (33), U7.K2 (LCD_DATA10)
unnamed: R26.8 (88), U7.K1 (LCD_DATA11)
unnamed: R26.2 (22), U7.L3 (LCD_DATA12)
unnamed: R26.9 (99), U7.L2 (LCD_DATA13)
unnamed: R24.2 (22), U7.L1 (LCD_DATA14)
unnamed: R26.1 (11), U7.M3 (LCD_DATA15)
unnamed: R26.6 (66), U7.J2 (LCD_DATA7)
unnamed: C10.1, C12.1, U3.C2 (VDDI)
unnamed: R9.7 (77), U3.A3 (D0), U7.R3 (GPMC_AD0)
unnamed: R9.8 (88), U3.A4 (D1), U7.R2 (GPMC_AD1)
unnamed: R9.3 (33), U3.A5 (D2), U7.R1 (GPMC_AD2)
unnamed: R9.2 (22), U3.B2 (D3), U7.T3 (GPMC_AD3)
unnamed: R9.1 (11), U3.B3 (D4), U7.T2 (GPMC_AD4)
unnamed: R9.9 (99), U3.B4 (D5), U7.T1 (GPMC_AD5)
unnamed: R10.1 (11), U3.B5 (D6), U7.P4 (GPMC_AD6)
unnamed: R9.4 (44), U3.B6 (D7), U7.R4 (GPMC_AD7)
unnamed: R9.6 (66), U3.M5 (CMD), U7.P1 (GPMC_CSN2)
unnamed: R10.9 (99), U3.M6 (SCK), U7.P2 (GPMC_CSN1)
unnamed: R10.2 (22), U3.K5 (!RST!), U7.R13 (GPMC_A4)
unnamed: R2.1, U7.P13 (GPMC_A5)
unnamed: R3.1, U7.T14 (GPMC_A6)
unnamed: R4.1, U7.R14 (GPMC_A7)
unnamed: R5.1, U7.P14 (GPMC_A8)
PA_ENABLE: TP11.1, U7.H16 (MII1_TX_CLK); also elsewhere on the board
UART0_RX: TP146.1, U7.A12 (UART0_RXD); also elsewhere on the board
UART0_TX: TP142.1, U7.B12 (UART0_TXD); also elsewhere on the board

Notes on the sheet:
SYSBOOT Jumper to config boot order must use very light pullups because boot config is latched at boot and then the pins a used for other purposes
SYSBOOT[15 : 5] == 0b0100_0000_000
Boot SD SYSBOOT[4 : 0] == 0b11000 SPI0 -> MMC0 -> USB0 -> UART0 Boot eMMC SYSBOOT[4 : 0] == 0b11100 MMC1 -> MMC0 -> UART0 -> USB0
USR LEDs
These capacitor values have varied slightly in the different designs I have looked at, but these values should be fine
eMMC Circuit
SD Card Circuit pinout from RED board
SYSBOOT Circuit
CAN Transceiver
CAN1 RX --> B11 --> UART1_TXD CAN1 TX --> A11 --> UART1_RXD
GPIO -> PIN map gpio3_9 == mii1_tx_clk gpio0_28 == mii1_txd0 gpio0_21 == mii1_txd1 gpio0_17 == mii1_txd2 gpio0_16 == mii1_txd3 gpio3_3 == mii1_tx_en gpio3_1 == mii1_crs gpio3_0 == mii1_col gpio3_10 == mii1_rx_clk gpio2_21 == mii1_rxd0 gpio2_20 == mii1_rxd1 gpio2_19 == mii1_rxd2 gpio2_18 == mii1_rxd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
NOTE: All these signals are outputs with the exception of FLASH. Likewise, I put the outputs on GPIO2,3 and inputs on GPIO0. I am not sure if this is better, but it seemed logical
Need ~2.2uF here, but using two 1uF for simplicity
Default Sysboot Pins SYSBOOT[4 : 0] == 0b11x00 SYSBOOT[2] HIGH == eMMC SYSBOOT[2] LOW == SD Card
SPI Flash/EEPROM For SPI boot DNP for now
OreSat DxWiFi: eMMC, SD card
1.1

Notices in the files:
parts and their libraries:
SparkFun-Hardware: Licensing: Creative Commons ShareAlike 4.0 International - https://creativecommons.org/licenses/by-sa/4.0
J-JST-SM06B-SRSS-TB: COPYRIGHT: Copyright (C) 2018 Accelerated Designs. All rights reserved
dicons: Copyright (C) 2004, Bob Starr (rtzaudio@mindspring.com)
